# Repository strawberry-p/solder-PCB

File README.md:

## Function
This is a PCB that converts a binary number input into a single logic high line on the output. It can be used to drive a stepper motor with less MCU pins.
## Images
### Schematic

The schematic has an unpopulated section of an additional layer. Since the solder kit doesn't have this many transistors and I lacked PCB space, I decided to use hex inverter ICs (which I can get for cheap) for the same inverter->inverter function.

I decided to make my own symbol for the IC (according to the datasheets) so that I don't mess up the wiring:

## PCB

The PCB has a lot of broken out pins for the single-line output. It also has LEDs for easier testing, and footprints for the ICs I will buy myself.
## 3D render

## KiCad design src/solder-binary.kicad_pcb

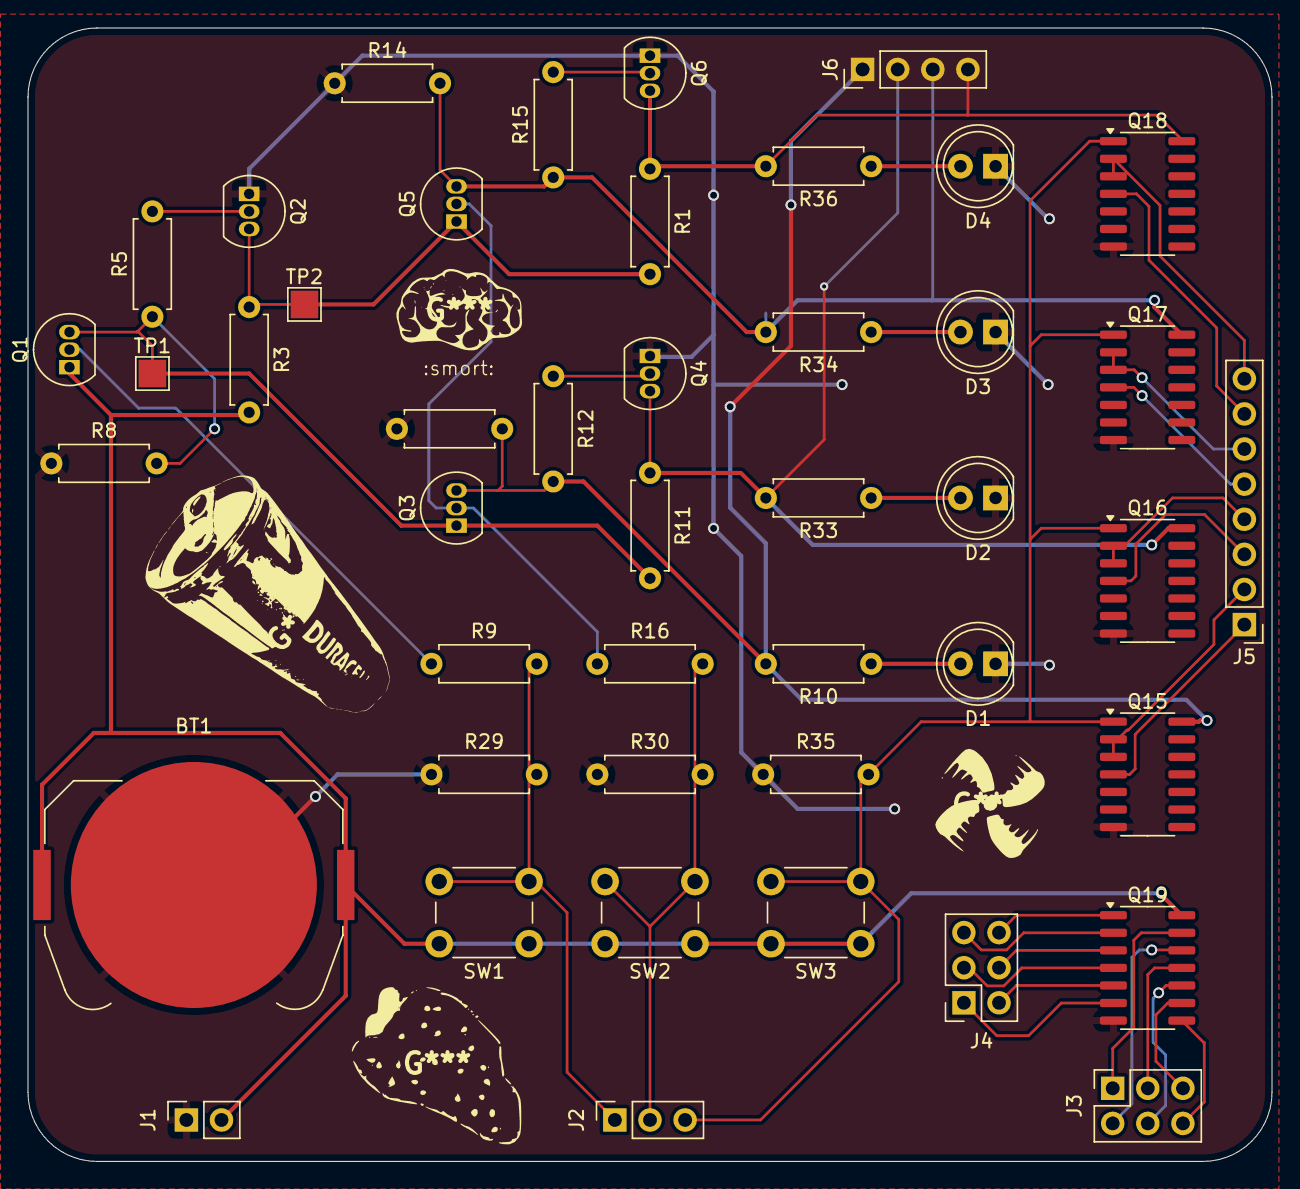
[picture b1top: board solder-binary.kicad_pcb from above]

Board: 2 copper layers, 90.0 x 82.0 mm, 45 parts (0 on the bottom side), 40 nets.

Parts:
BT1: Battery_Cell; BatteryHolder_Keystone_3034_1x20mm
D1, D2, D3, D4: LED; LED_D5.0mm
J1: Energy; PinSocket_1x02_P2.54mm_Vertical
J2: Conn_01x03_Socket; PinSocket_1x03_P2.54mm_Vertical
J3, J4: Conn_01x06_Socket; PinSocket_2x03_P2.54mm_Vertical
J5: Conn_02x04_Odd_Even; PinHeader_1x08_P2.54mm_Vertical
J6: Conn_01x04_Pin; PinHeader_1x04_P2.54mm_Vertical
Q1, Q3, Q5: 2N3906; TO-92_Inline
Q2, Q4, Q6: 2N3904; TO-92_Inline
Q15, Q16, Q17, Q18, Q19: SO-14_3.9x8.65mm_P1.27mm
R1, R3, R11: 90Ohm; R_Axial_DIN0207_L6.3mm_D2.5mm_P7.62mm_Horizontal
R5, R9, R12, R15, R16: 4.7K; R_Axial_DIN0207_L6.3mm_D2.5mm_P7.62mm_Horizontal
R8, R13, R14, R29, R30, R35: 47K; R_Axial_DIN0207_L6.3mm_D2.5mm_P7.62mm_Horizontal
R10, R33, R34, R36: 51Ohm; R_Axial_DIN0207_L6.3mm_D2.5mm_P7.62mm_Horizontal
SW1, SW2, SW3: SW_Push_45deg; SW_PUSH_6mm
TP1, TP2: TestPoint; TestPoint_Pad_2.0x2.0mm

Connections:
+1V5: BT1.1 (+), J1.2, Q1.1 (E), Q19.14 (Vcc), R3.2, SW1.1, SW2.1, SW3.1
B0: J2.1, R9.2, R29.2, SW1.2
B2: J2.2, R16.2, R30.2, SW2.2
B4: J2.3, Q15.1 (1A), Q16.1 (1A), Q17.1 (1A), Q18.1 (1A), R35.2, SW3.2
GND: BT1.2 (-), D1.1 (K), D2.1 (K), D3.1 (K), D4.1 (K), J1.1, Q2.1 (E), Q4.1 (E), Q6.1 (E), Q15.7 (GND), Q16.7 (GND), Q17.7 (GND), Q18.7 (GND), Q19.7 (GND), R8.1, R13.1, R14.1, R29.1, R30.1, R35.1
IN2: Q1.3 (C), Q3.1 (E), R5.1, R8.2, R11.2, TP1.1
IN4: Q2.3 (C), Q5.1 (E), R1.2, R3.1, TP2.1
IN6: J6.1, Q3.3 (C), Q15.14 (Vcc), R10.2, R12.2, R13.2
IN8: J6.2, Q4.3 (C), Q16.14 (Vcc), R11.1, R33.2
IN10: J6.3, Q5.3 (C), Q17.14 (Vcc), R14.2, R15.1, R34.2
IN12: J6.4, Q6.3 (C), Q18.14 (Vcc), R1.1, R36.2
unnamed: D1.2 (A), R10.1
unnamed: D2.2 (A), R33.1
unnamed: D3.2 (A), R34.1
unnamed: D4.2 (A), R36.1
unnamed: J3.1, Q19.13 (6A)
unnamed: J3.2, Q19.12 (6Y)
unnamed: J3.3, Q19.11 (5A)
unnamed: J3.4, Q19.10 (5Y)
unnamed: J3.5, Q19.9 (4A)
unnamed: J3.6, Q19.8 (4Y)
unnamed: J4.1, Q19.6 (3Y)
unnamed: J4.2, Q19.5 (3A)
unnamed: J4.3, Q19.4 (2Y)
unnamed: J4.4, Q19.3 (2A)
unnamed: J4.5, Q19.2 (1Y)
unnamed: J4.6, Q19.1 (1A)
unnamed: Q1.2 (B), R9.1
unnamed: Q2.2 (B), R5.2
unnamed: Q3.2 (B), Q5.2 (B), R16.1
unnamed: Q4.2 (B), R12.1
unnamed: Q6.2 (B), R15.2
O6: J5.2, Q15.2 (1Y), Q15.3 (2A)
O7: J5.1, Q15.4 (2Y)
O8: J5.4, Q16.2 (1Y), Q16.3 (2A)
O9: J5.3, Q16.4 (2Y)
O10: J5.6, Q17.2 (1Y), Q17.3 (2A)
O11: J5.5, Q17.4 (2Y)
O12: J5.8, Q18.2 (1Y), Q18.3 (2A)
O13: J5.7, Q18.4 (2Y)

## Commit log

2025-07-02 add src folder
2025-07-02 Add source files
2025-07-02 Update source files with silkscreen
2025-07-02 Add img folder
2025-07-02 Add images to repo
2025-07-02 Add repo images to README
    replaces github userfiles links
2025-07-02 Update README.md
    add more newlines
